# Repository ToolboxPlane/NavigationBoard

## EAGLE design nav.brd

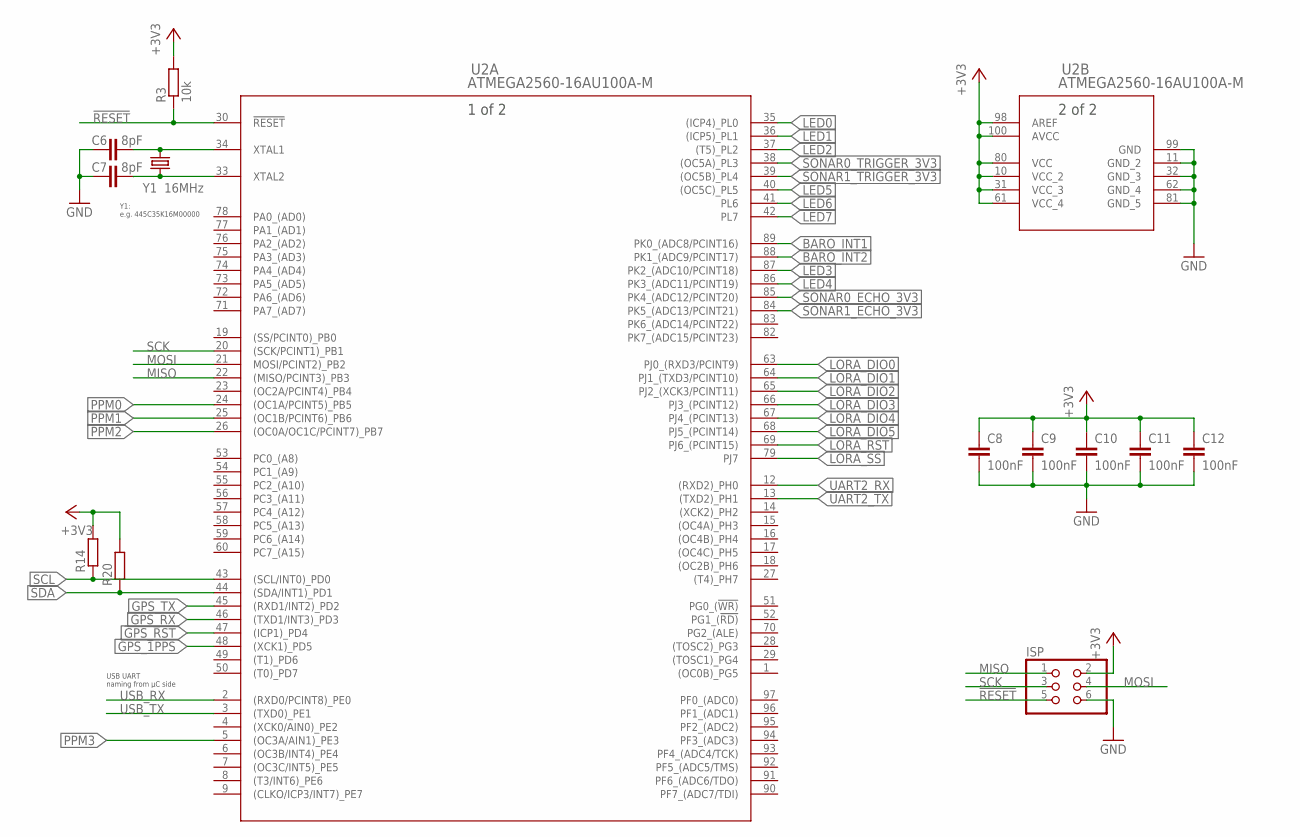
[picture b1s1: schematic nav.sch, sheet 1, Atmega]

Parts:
C6, C7: 8pF; C0603
C8, C9, C10, C11, C12: 100nF; C0603
ISP: PINHD-2X3; 2X03
R3: 10k; R0603
R14, R20: R-EU_R0603; R0603
U2: ATMEGA2560-16AU100A-M; 100A-M
Y1: 16MHz; CRYSTAL-SMD-5X3.2-2PAD

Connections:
!GPS_RST: U2.47 ((ICP1)_PD4); also elsewhere on the board
!LORA_RST: U2.69 (PJ6_(PCINT15)); also elsewhere on the board
!LORA_SS: U2.79 (PJ7); also elsewhere on the board
!RESET: ISP.5, R3.1, U2.30 (!RESET); also elsewhere on the board
+3V3: C8.1, C9.1, C10.1, C11.1, C12.1, ISP.2, R3.2, R14.2, R20.2, U2.10 (VCC_2), U2.31 (VCC_3), U2.61 (VCC_4), U2.80 (VCC), U2.98 (AREF), U2.100 (AVCC); also elsewhere on the board
BARO_INT1: U2.89 (PK0_(ADC8/PCINT16)); also elsewhere on the board
BARO_INT2: U2.88 (PK1_(ADC9/PCINT17)); also elsewhere on the board
GND: C6.1, C7.1, C8.2, C9.2, C10.2, C11.2, C12.2, ISP.6, U2.11 (GND_2), U2.32 (GND_3), U2.62 (GND_4), U2.81 (GND_5), U2.99 (GND); also elsewhere on the board
GPS_1PPS: U2.48 ((XCK1)_PD5); also elsewhere on the board
GPS_RX: U2.46 ((TXD1/INT3)_PD3); also elsewhere on the board
GPS_TX: U2.45 ((RXD1/INT2)_PD2); also elsewhere on the board
LED0: U2.35 ((ICP4)_PL0); also elsewhere on the board
LED1: U2.36 ((ICP5)_PL1); also elsewhere on the board
LED2: U2.37 ((T5)_PL2); also elsewhere on the board
LED3: U2.87 (PK2_(ADC10/PCINT18)); also elsewhere on the board
LED4: U2.86 (PK3_(ADC11/PCINT19)); also elsewhere on the board
LED5: U2.40 ((OC5C)_PL5); also elsewhere on the board
LED6: U2.41 (PL6); also elsewhere on the board
LED7: U2.42 (PL7); also elsewhere on the board
LORA_DIO0: U2.63 (PJ0_(RXD3/PCINT9)); also elsewhere on the board
LORA_DIO1: U2.64 (PJ1_(TXD3/PCINT10)); also elsewhere on the board
LORA_DIO2: U2.65 (PJ2_(XCK3/PCINT11)); also elsewhere on the board
LORA_DIO3: U2.66 (PJ3_(PCINT12)); also elsewhere on the board
LORA_DIO4: U2.67 (PJ4_(PCINT13)); also elsewhere on the board
LORA_DIO5: U2.68 (PJ5_(PCINT14)); also elsewhere on the board
MISO: ISP.1, U2.22 ((MISO/PCINT3)_PB3); also elsewhere on the board
MOSI: ISP.4, U2.21 (MOSI/PCINT2)_PB2); also elsewhere on the board
unnamed: C6.2, U2.34 (XTAL1), Y1.P$2 (2)
unnamed: C7.2, U2.33 (XTAL2), Y1.P$1 (1)
PPM0: U2.24 ((OC1A/PCINT5)_PB5); also elsewhere on the board
PPM1: U2.25 ((OC1B/PCINT6)_PB6); also elsewhere on the board
PPM2: U2.26 ((OC0A/OC1C/PCINT7)_PB7); also elsewhere on the board
PPM3: U2.5 ((OC3A/AIN1)_PE3); also elsewhere on the board
SCK: ISP.3, U2.20 ((SCK/PCINT1)_PB1); also elsewhere on the board
SCL: R14.1, U2.43 ((SCL/INT0)_PD0); also elsewhere on the board
SDA: R20.1, U2.44 ((SDA/INT1)_PD1); also elsewhere on the board
SONAR0_ECHO_3V3: U2.85 (PK4_(ADC12/PCINT20)); also elsewhere on the board
SONAR0_TRIGGER_3V3: U2.38 ((OC5A)_PL3); also elsewhere on the board
SONAR1_ECHO_3V3: U2.84 (PK5_(ADC13/PCINT21)); also elsewhere on the board
SONAR1_TRIGGER_3V3: U2.39 ((OC5B)_PL4); also elsewhere on the board
UART2_RX: U2.12 ((RXD2)_PH0); also elsewhere on the board
UART2_TX: U2.13 ((TXD2)_PH1); also elsewhere on the board
USB_RX: U2.2 ((RXD0/PCINT8)_PE0); also elsewhere on the board
USB_TX: U2.3 ((TXD0)_PE1); also elsewhere on the board

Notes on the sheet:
Y1: e.g. 445C35K16M00000
USB UART naming from µC side

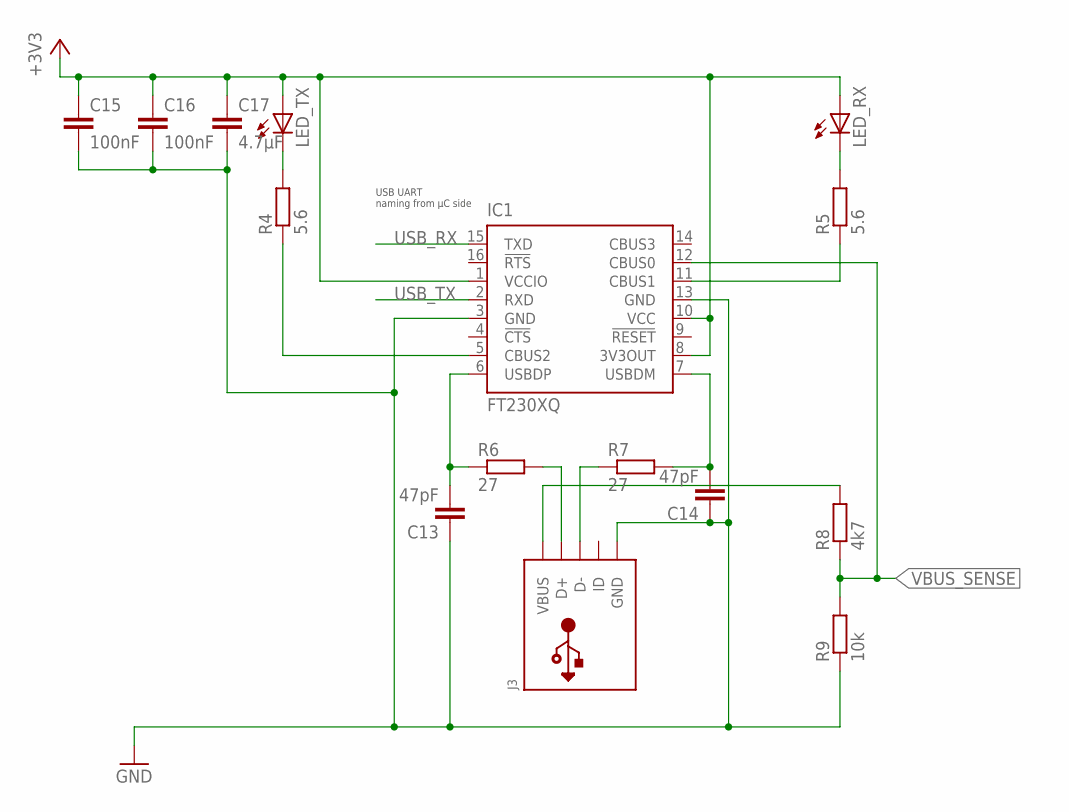
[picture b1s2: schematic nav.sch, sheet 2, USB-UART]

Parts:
C13, C14: 47pF; C0603
C15, C16: 100nF; C0603
C17: 4.7µF; C0603
IC1: FT230XQ; QFN16
J3: USBMINIB; USB-MINIB
LED_RX: LEDCHIP-LED0603; CHIP-LED0603
LED_TX: LEDCHIP-LED0603; CHIP-LED0603
R4, R5: 5.6; R0603
R6, R7: 27; R0603
R8: 4k7; R0603
R9: 10k; R0603

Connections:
+3V3: C15.1, C16.1, C17.1, IC1.1 (VCCIO), IC1.8 (3V3OUT), IC1.10 (VCC), LED_RX.A, LED_TX.A; also elsewhere on the board
GND: C13.1, C14.1, C15.2, C16.2, C17.2, IC1.3 (GND), IC1.13 (GND), J3.GND, R9.1; also elsewhere on the board
unnamed: C13.2, IC1.6 (USBDP), R6.1
unnamed: C14.2, IC1.7 (USBDM), R7.2
unnamed: IC1.5 (CBUS2), R4.1
unnamed: IC1.11 (CBUS1), R5.1
unnamed: LED_TX.C, R4.2
unnamed: LED_RX.C, R5.2
unnamed: J3.D+, R6.2
unnamed: J3.D-, R7.1
unnamed: J3.VBUS, R8.2
USB_RX: IC1.15 (TXD); also elsewhere on the board
USB_TX: IC1.2 (RXD); also elsewhere on the board
VBUS_SENSE: IC1.12 (CBUS0), R8.1, R9.2

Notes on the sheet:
USB UART naming from µC side

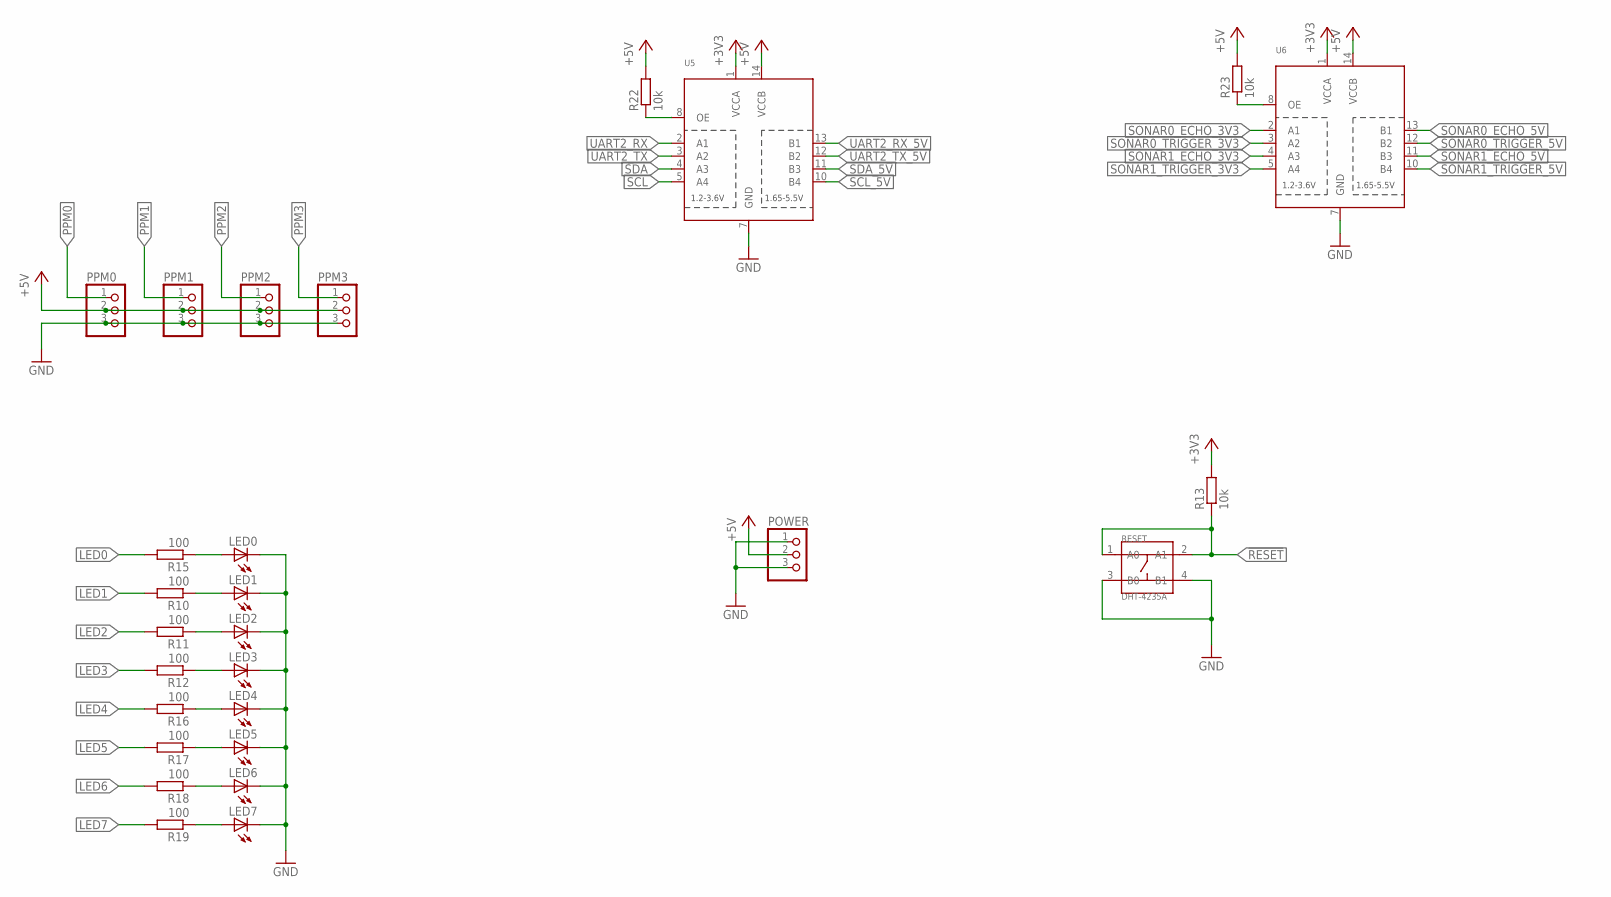
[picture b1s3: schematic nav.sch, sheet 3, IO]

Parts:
LED0, LED1, LED2, LED3, LED4, LED5, LED6, LED7: LEDCHIP-LED0603; CHIP-LED0603
POWER: PINHD-1X3; 1X03
PPM0, PPM1, PPM2, PPM3: PINHD-1X3; 1X03
R10, R11, R12, R15, R16, R17, R18, R19: 100; R0603
R13, R22, R23: 10k; R0603
RESET: DHT-4235A; SW4-SMD-4.2X3.2X2.5MM
U5, U6: TXB0104PWR; TSSOP14

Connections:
!RESET: R13.1, RESET.1 (A0), RESET.2 (A1); also elsewhere on the board
+3V3: R13.2, U5.1 (VCCA), U6.1 (VCCA); also elsewhere on the board
+5V: POWER.2, PPM0.2, PPM1.2, PPM2.2, PPM3.2, R22.2, R23.2, U5.14 (VCCB), U6.14 (VCCB); also elsewhere on the board
GND: LED0.C, LED1.C, LED2.C, LED3.C, LED4.C, LED5.C, LED6.C, LED7.C, POWER.1, POWER.3, PPM0.3, PPM1.3, PPM2.3, PPM3.3, RESET.3 (B0), RESET.4 (B1), U5.7 (GND), U6.7 (GND); also elsewhere on the board
LED0: R15.2; also elsewhere on the board
LED1: R10.2; also elsewhere on the board
LED2: R11.2; also elsewhere on the board
LED3: R12.2; also elsewhere on the board
LED4: R16.2; also elsewhere on the board
LED5: R17.2; also elsewhere on the board
LED6: R18.2; also elsewhere on the board
LED7: R19.2; also elsewhere on the board
unnamed: LED1.A, R10.1
unnamed: LED2.A, R11.1
unnamed: LED3.A, R12.1
unnamed: LED4.A, R16.1
unnamed: LED5.A, R17.1
unnamed: LED6.A, R18.1
unnamed: LED7.A, R19.1
unnamed: LED0.A, R15.1
unnamed: R23.1, U6.8 (OE)
unnamed: R22.1, U5.8 (OE)
PPM0: PPM0.1; also elsewhere on the board
PPM1: PPM1.1; also elsewhere on the board
PPM2: PPM2.1; also elsewhere on the board
PPM3: PPM3.1; also elsewhere on the board
SCL: U5.5 (A4); also elsewhere on the board
SCL_5V: U5.10 (B4); also elsewhere on the board
SDA: U5.4 (A3); also elsewhere on the board
SDA_5V: U5.11 (B3); also elsewhere on the board
SONAR0_ECHO_3V3: U6.2 (A1); also elsewhere on the board
SONAR0_ECHO_5V: U6.13 (B1); also elsewhere on the board
SONAR0_TRIGGER_3V3: U6.3 (A2); also elsewhere on the board
SONAR0_TRIGGER_5V: U6.12 (B2); also elsewhere on the board
SONAR1_ECHO_3V3: U6.4 (A3); also elsewhere on the board
SONAR1_ECHO_5V: U6.11 (B3); also elsewhere on the board
SONAR1_TRIGGER_3V3: U6.5 (A4); also elsewhere on the board
SONAR1_TRIGGER_5V: U6.10 (B4); also elsewhere on the board
UART2_RX: U5.2 (A1); also elsewhere on the board
UART2_RX_5V: U5.13 (B1); also elsewhere on the board
UART2_TX: U5.3 (A2); also elsewhere on the board
UART2_TX_5V: U5.12 (B2); also elsewhere on the board

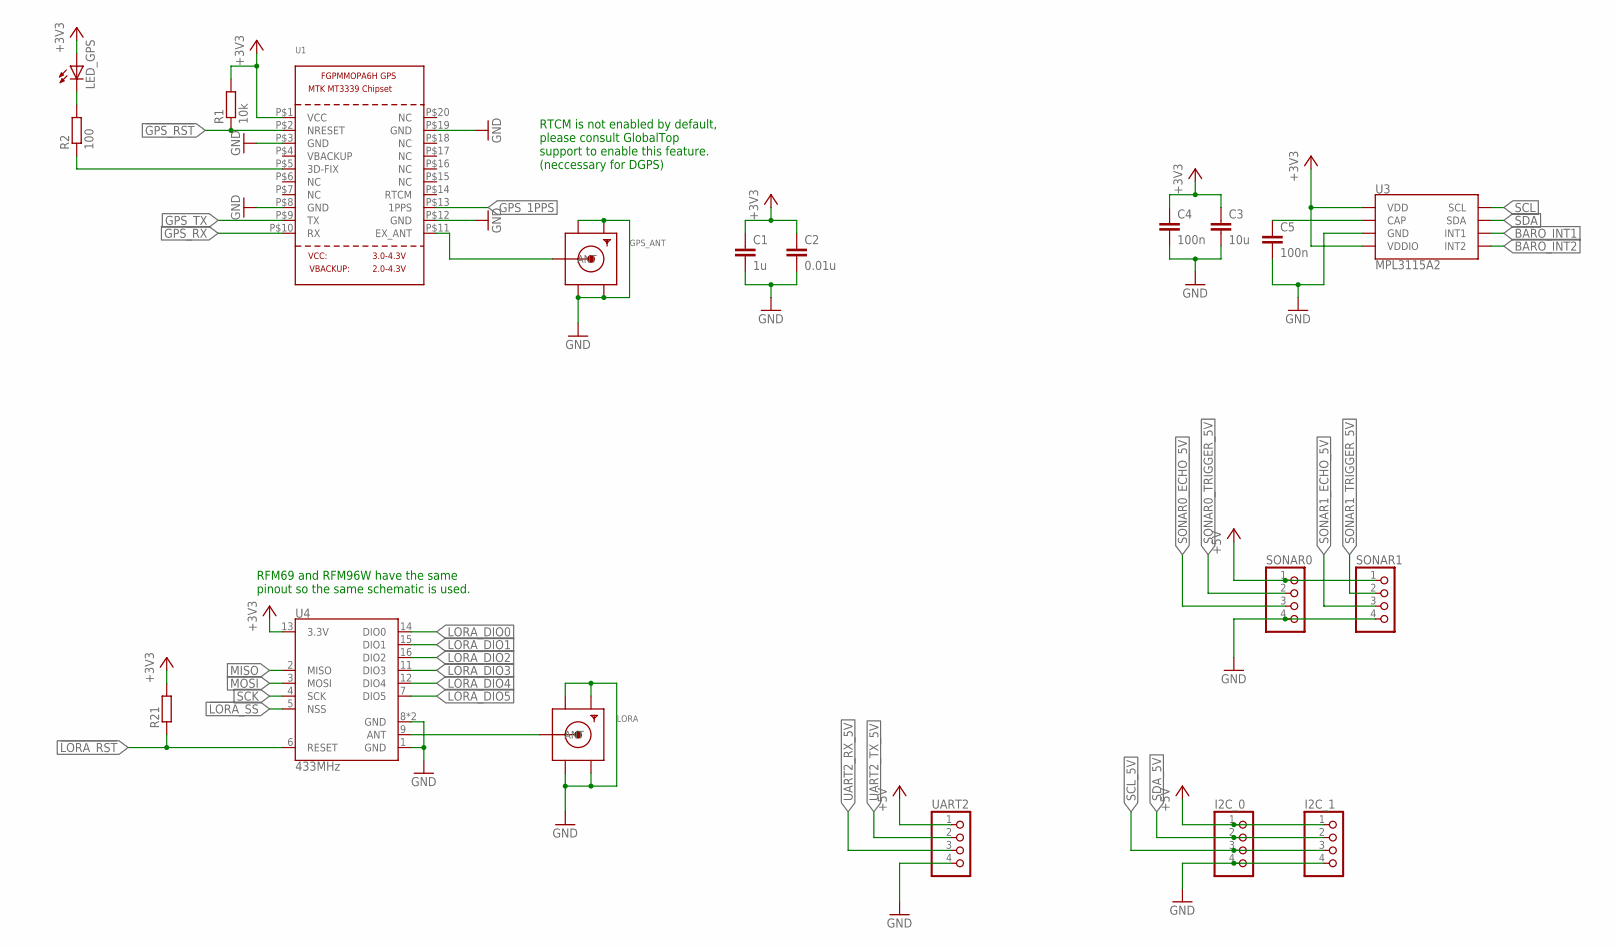
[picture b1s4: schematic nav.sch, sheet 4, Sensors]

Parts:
C1: 1u; C0603
C2: 0.01u; C0603
C3: 10u; C0603
C4, C5: 100n; C0603
GPS_ANT: SMACONNECTOR_EDGE; SMA_EDGELAUNCH
I2C_0, I2C_1: PINHD-1X4; 1X04
LED_GPS: LEDCHIP-LED0603; CHIP-LED0603
LORA: SMACONNECTOR_EDGE; SMA_EDGELAUNCH
R1: 10k; R0603
R2: 100; R0603
R21: R-EU_R0603; R0603
SONAR0, SONAR1: PINHD-1X4; 1X04
U1: GPS_FGPMMOPA6H; FGPMMOPA6H
U3: MPL3115A2; LGA-8-5X3
U4: 433MHz; RFM69HCW-XXXS2
UART2: PINHD-1X4; 1X04

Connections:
!GPS_RST: R1.1, U1.P$2 (NRESET); also elsewhere on the board
!LORA_RST: R21.1, U4.6 (RESET); also elsewhere on the board
!LORA_SS: U4.5 (NSS); also elsewhere on the board
+3V3: C1.1, C2.1, C3.1, C4.1, LED_GPS.A, R1.2, R21.2, U1.P$1 (VCC), U3.1 (VDD), U3.4 (VDDIO), U4.13 (3.3V); also elsewhere on the board
+5V: I2C_0.1, I2C_1.1, SONAR0.1, SONAR1.1, UART2.1; also elsewhere on the board
BARO_INT1: U3.6 (INT1); also elsewhere on the board
BARO_INT2: U3.5 (INT2); also elsewhere on the board
GND: C1.2, C2.2, C3.2, C4.2, C5.2, GPS_ANT.GND@1 (GND4), GPS_ANT.GND@2 (GND3), GPS_ANT.GND@3 (GND2), GPS_ANT.GND@4 (GND1), I2C_0.4, I2C_1.4, LORA.GND@1 (GND4), LORA.GND@2 (GND3), LORA.GND@3 (GND2), LORA.GND@4 (GND1), SONAR0.4, SONAR1.4, U1.P$3 (GND), U1.P$8 (GND), U1.P$12 (GND), U1.P$19 (GND), U3.3 (GND), U4.1 (GND), U4.8 (GND), U4.10 (GND), UART2.4; also elsewhere on the board
GPS_1PPS: U1.P$13 (1PPS); also elsewhere on the board
GPS_RX: U1.P$10 (RX); also elsewhere on the board
GPS_TX: U1.P$9 (TX); also elsewhere on the board
LORA_DIO0: U4.14 (DIO0); also elsewhere on the board
LORA_DIO1: U4.15 (DIO1); also elsewhere on the board
LORA_DIO2: U4.16 (DIO2); also elsewhere on the board
LORA_DIO3: U4.11 (DIO3); also elsewhere on the board
LORA_DIO4: U4.12 (DIO4); also elsewhere on the board
LORA_DIO5: U4.7 (DIO5); also elsewhere on the board
MISO: U4.2 (MISO); also elsewhere on the board
MOSI: U4.3 (MOSI); also elsewhere on the board
unnamed: GPS_ANT.P (ANT), U1.P$11 (EX_ANT)
unnamed: R2.1, U1.P$5 (3D-FIX)
unnamed: LED_GPS.C, R2.2
unnamed: C5.1, U3.2 (CAP)
unnamed: LORA.P (ANT), U4.9 (ANT)
SCK: U4.4 (SCK); also elsewhere on the board
SCL: U3.8 (SCL); also elsewhere on the board
SCL_5V: I2C_0.3, I2C_1.3; also elsewhere on the board
SDA: U3.7 (SDA); also elsewhere on the board
SDA_5V: I2C_0.2, I2C_1.2; also elsewhere on the board
SONAR0_ECHO_5V: SONAR0.3; also elsewhere on the board
SONAR0_TRIGGER_5V: SONAR0.2; also elsewhere on the board
SONAR1_ECHO_5V: SONAR1.3; also elsewhere on the board
SONAR1_TRIGGER_5V: SONAR1.2; also elsewhere on the board
UART2_RX_5V: UART2.3; also elsewhere on the board
UART2_TX_5V: UART2.2; also elsewhere on the board

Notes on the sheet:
RTCM is not enabled by default, please consult GlobalTop support to enable this feature. (neccessary for DGPS)
RFM69 and RFM96W have the same pinout so the same schematic is used.

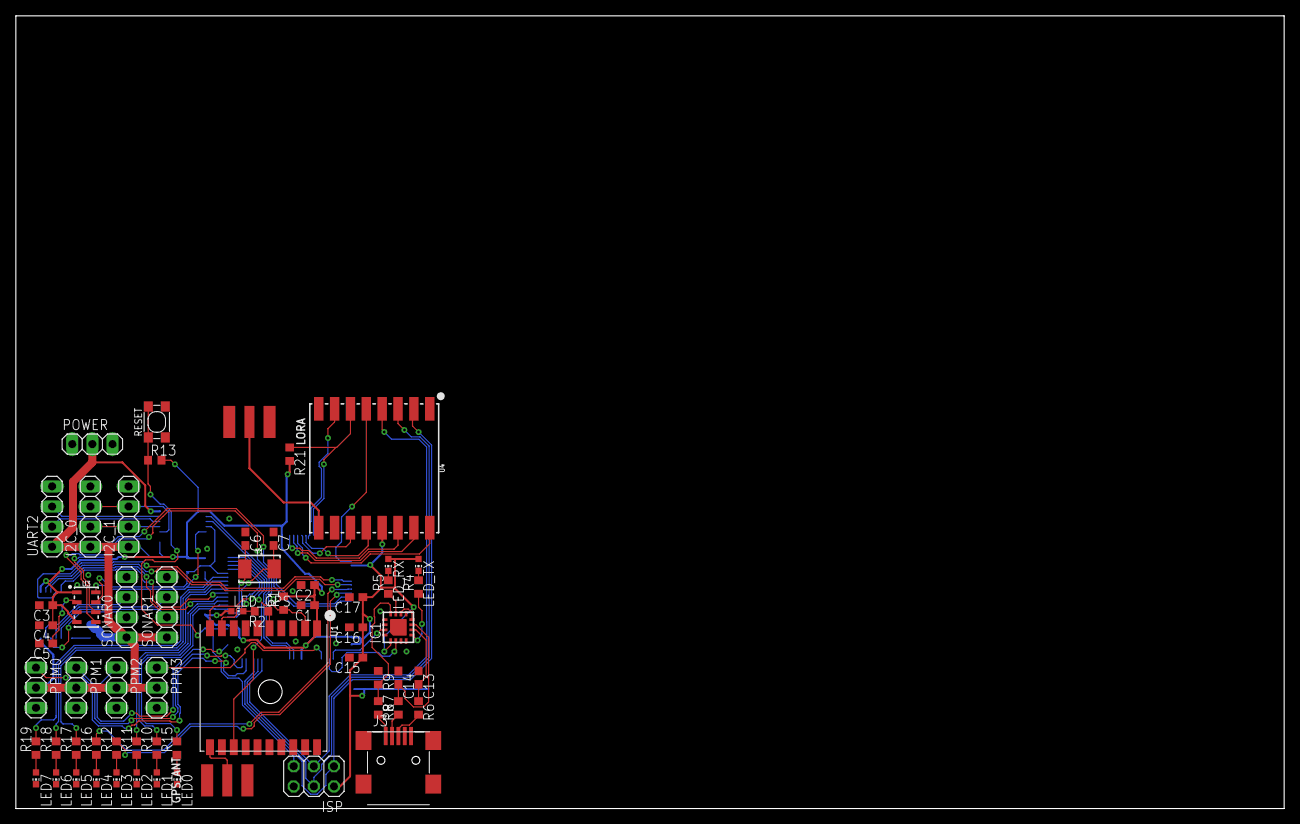
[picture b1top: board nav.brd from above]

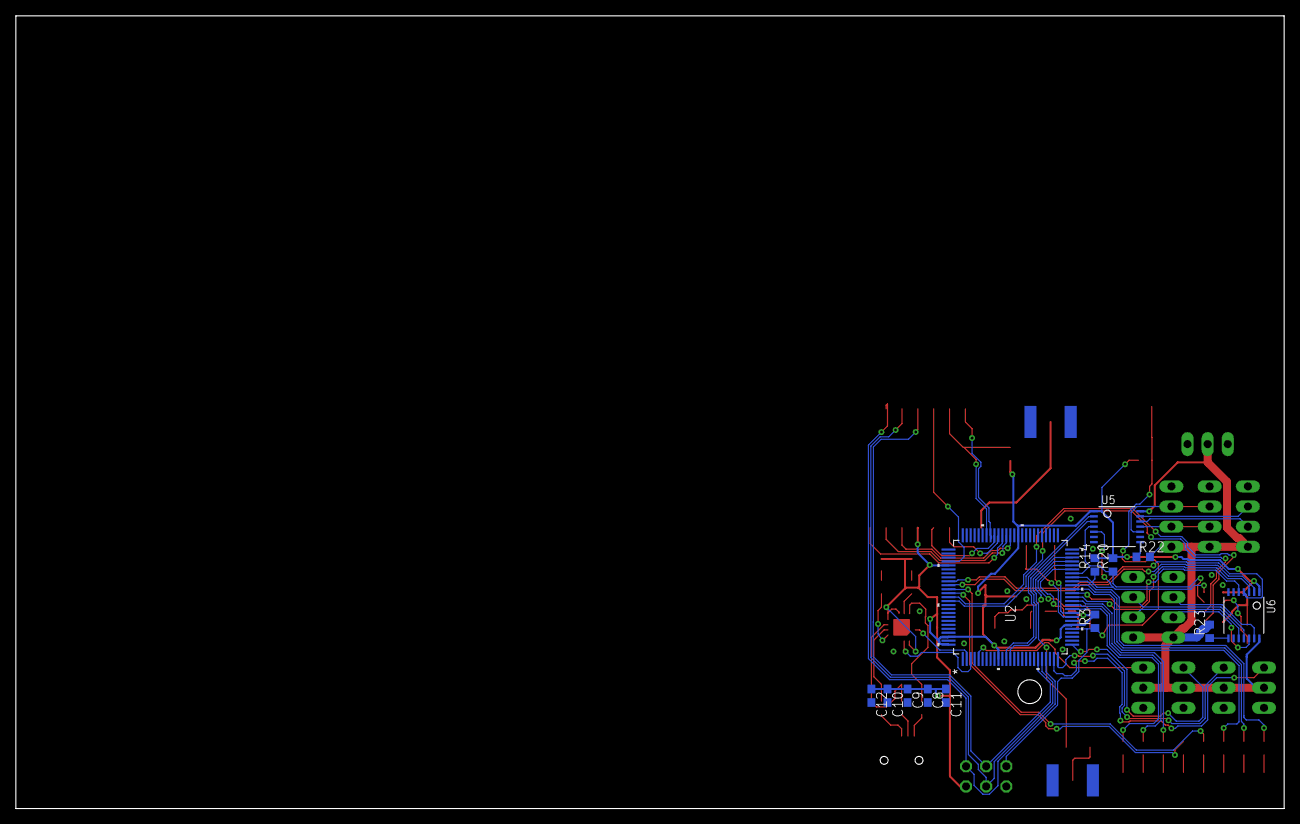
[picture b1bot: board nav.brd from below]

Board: 2 copper layers, 160.0 x 100.0 mm, 74 parts (13 on the bottom side), 78 nets.

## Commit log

2018-10-21 Added GPS
2018-10-21 Added gitignore
2018-10-21 Added Barometer
2018-10-21 Added LoRa
2018-10-21 Added Connectors for HC-SR04, UART3 and I2C
2018-10-21 First draft of the layout finished
2019-04-26 kicad und so
2019-04-26 ft230 annotation
2020-03-30 KiCad gitignore, add project file
2020-03-30 remove L86, fix Lora symbol
2020-03-30 update FT230 submodule
2020-03-30 3V regulator, crystal oscillator, reset switch, new GPS
2020-03-30 update ft230
2020-03-30 add ISP, MPL3115A2
2020-07-27 no clue, this has been >4 months and diff is kinda useless here...
2020-07-28 Erster Grober Entwurf
2020-07-28 Kleinerer AVR-ISP Stecker
2020-07-30 Layout weiter gemacht
2020-08-01 Weniger Leiterbahnen auf der Oberseite
2020-08-03 XT 30 entfernt

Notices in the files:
parts and their libraries:
SparkFun-Clocks: Licensing: Creative Commons ShareAlike 4.0 International - https://creativecommons.org/licenses/by-sa/4.0
